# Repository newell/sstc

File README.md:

# sstc
This project is my design of a half-bridge Solid State Tesla Coil (SSTC).

An SSTC is a type of [Tesla coil](https://en.wikipedia.org/wiki/Tesla_coil) that uses modern semiconductor devices such as MOSFETs or IGBTs to generate high-frequency alternating current (AC) and high voltages. The term "half-bridge" refers to the specific configuration of the power electronics used in the coil.

## Tools Used for SSTC Design

- **[KiCad](https://github.com/KiCad)**: For schematic capture and PCB layout.
- **[build123d](https://github.com/gumyr/build123d)**: For CAD design.
- **[Prusa MK3S+](https://www.prusa3d.com/)**: 3D printer for printing the enclosure.

## How Half-Bridge SSTCs Work

1. **Power Supply**: The primary coil is powered by a DC power supply. This DC voltage is then switched on and off at a high frequency by the half-bridge circuit.

2. **Half-Bridge Configuration**:
   - **Half-Bridge Circuit**: The half-bridge circuit consists of two semiconductor switches (typically MOSFETs or IGBTs) and two capacitors. One switch is connected to the positive rail of the power supply, and the other switch is connected to the negative rail. The junction between the two switches connects to one end of the primary coil.
   - **Switching**: The switches are controlled in such a way that they turn on and off alternately. When one switch is on, it allows current to flow through the primary coil in one direction, and when the other switch is on, it allows current to flow in the opposite direction. This creates an alternating current (AC) in the primary coil.

3. **Resonant Circuit**: The primary coil and the primary capacitor form a resonant circuit. The switching frequency of the half-bridge circuit is typically set to match the resonant frequency of this LC circuit, which maximizes the energy transfer to the secondary coil.

4. **Secondary Coil**: The secondary coil, which is coupled to the primary coil via magnetic induction, has many more turns than the primary coil. This step-up transformer action increases the voltage to very high levels.

5. **Top Load**: The top load (usually a toroid) of the secondary coil helps to shape the electric field and allows the coil to produce long electrical discharges (sparks).

### Why It’s Called "Half-Bridge"

The term "half-bridge" comes from the structure of the circuit:
- **Full-Bridge vs. Half-Bridge**: In a full-bridge circuit, there are four switches arranged in an H-bridge configuration. This allows for full control over the direction of the current through the load (primary coil). In contrast, a half-bridge circuit uses only two switches and two capacitors. It controls the current direction by alternately switching the two switches, but only half of the H-bridge is implemented.
- **Simplified Design**: The half-bridge design is simpler and more cost-effective compared to a full-bridge design, making it a popular choice for SSTCs.

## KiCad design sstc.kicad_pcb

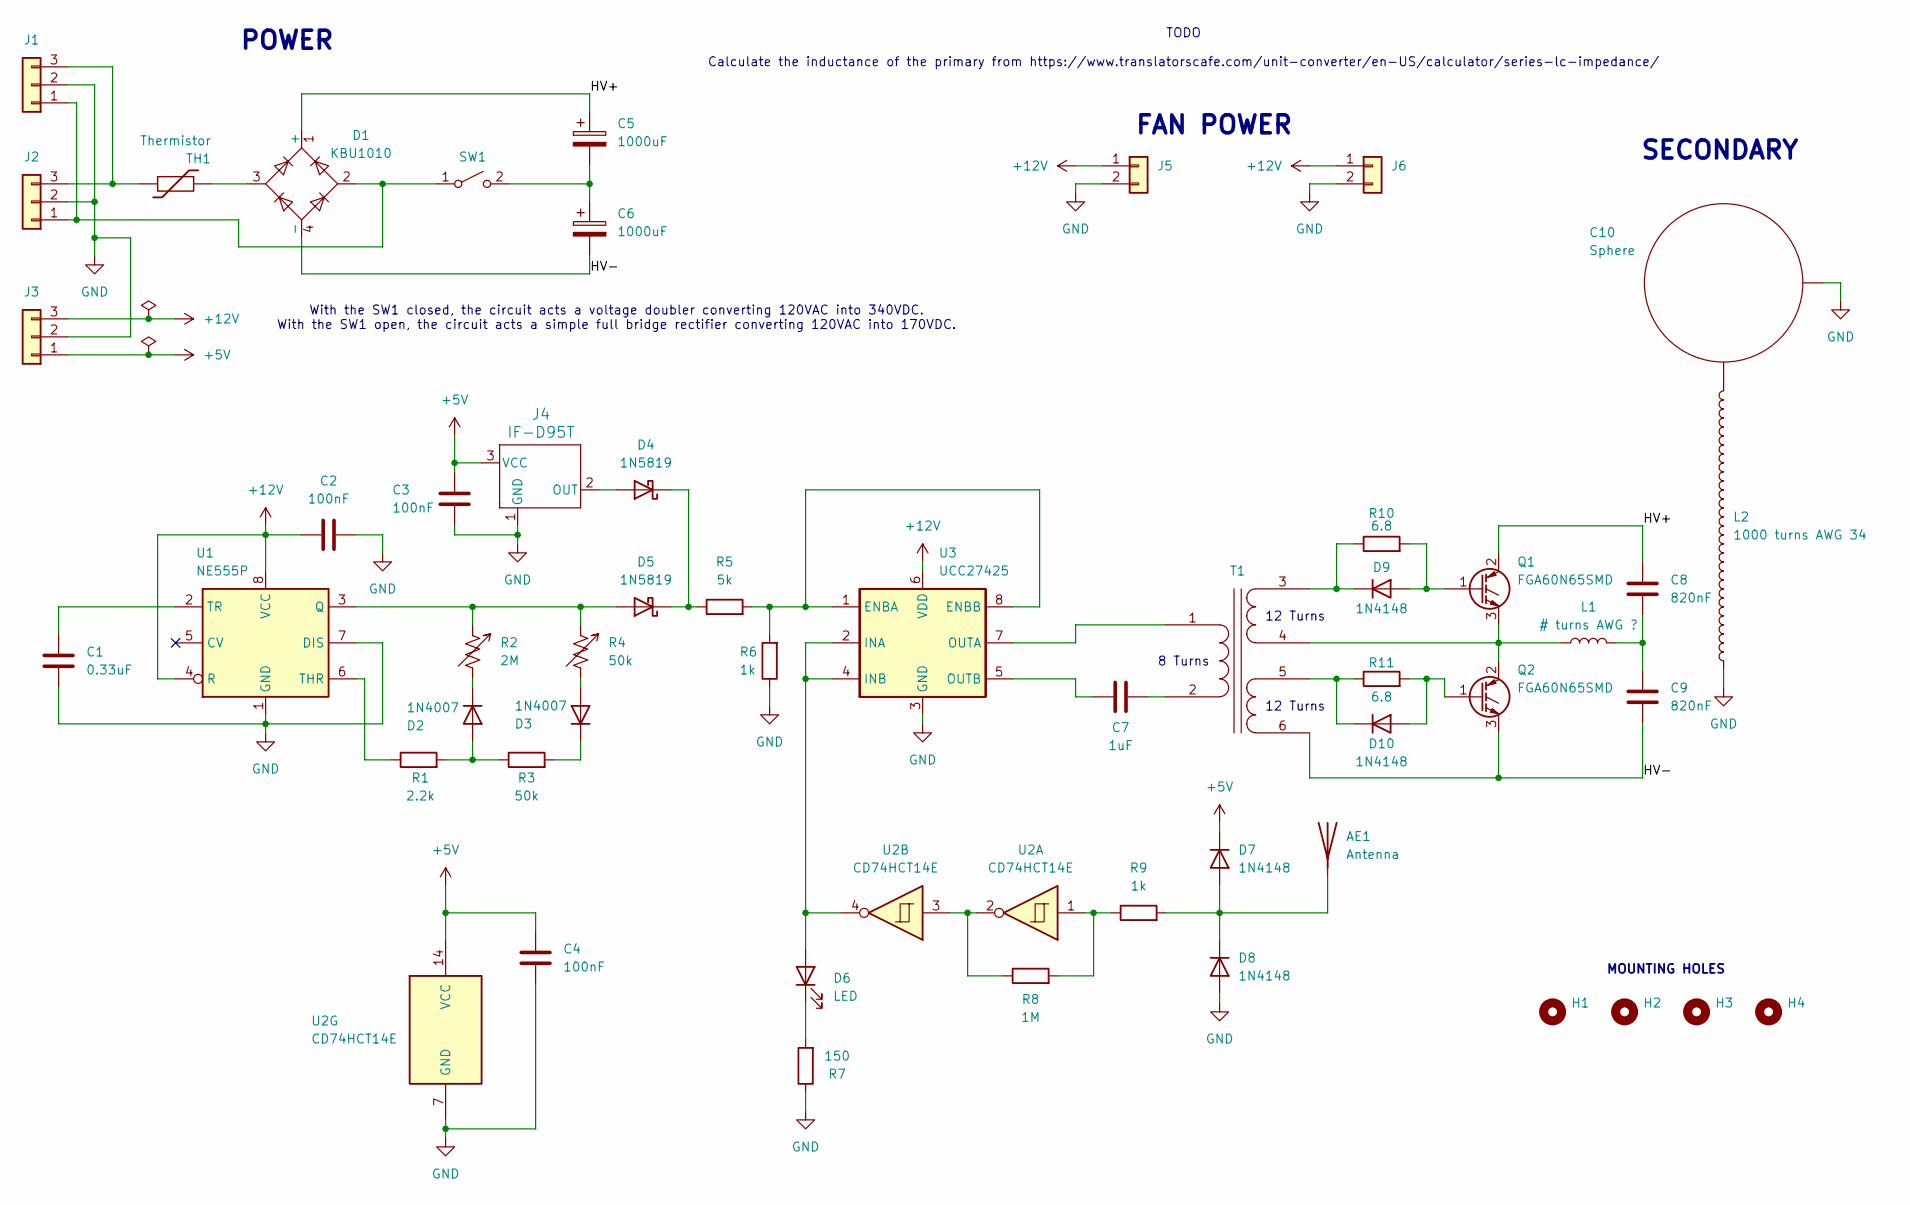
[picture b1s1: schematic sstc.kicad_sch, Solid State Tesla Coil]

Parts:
AE1: Antenna; SolderWire-1sqmm_1x01_D1.4mm_OD3.9mm
C1: 0.33uF; C_Rect_L7.0mm_W3.5mm_P5.00mm
C2, C3, C4: 100nF; C_Rect_L7.0mm_W3.5mm_P5.00mm
C5, C6: 1000uF; CP_Radial_D30.0mm_P10.00mm_SnapIn
C7: 1uF; C_Rect_L7.0mm_W3.5mm_P5.00mm
C8, C9: 820nF; C_Rect_L18.0mm_W11.0mm_P15.00mm_FKS3_FKP3
C10: Sphere
D1: KBU1010; Diode_Bridge_Vishay_KBU
D2, D3: 1N4007; D_DO-41_SOD81_P10.16mm_Horizontal
D4, D5: 1N5819; D_DO-41_SOD81_P10.16mm_Horizontal; Manufacturer_Part_Number 1N5819-TP
D6: LED; D_DO-35_SOD27_P7.62mm_Horizontal
D7, D8, D9, D10: 1N4148; D_DO-35_SOD27_P7.62mm_Horizontal
H1, H2, H3, H4: MountingHole; MountingHole_3.2mm_M3_ISO7380_Pad_TopBottom
J1, J2, J3: Conn_01x03; SolderWire-1sqmm_1x03_P7.8mm_D1.4mm_OD3.9mm
J4: IF-D95T; IF-D95T_IFB
J5, J6: Conn_01x02; JST_XH_B2B-XH-A_1x02_P2.50mm_Vertical
L1: # turns AWG ?; SolderWire-2sqmm_1x02_P7.8mm_D2mm_OD3.9mm
L2: 1000 turns AWG 34
Q1, Q2: FGA60N65SMD; TO-3P-3_Vertical
R1: 2.2k; R_Axial_DIN0614_L14.3mm_D5.7mm_P15.24mm_Horizontal
R2: 2M; R_Axial_DIN0614_L14.3mm_D5.7mm_P15.24mm_Horizontal
R3, R4: 50k; R_Axial_DIN0614_L14.3mm_D5.7mm_P15.24mm_Horizontal
R5: 5k; R_Axial_DIN0614_L14.3mm_D5.7mm_P15.24mm_Horizontal
R6, R9: 1k; R_Axial_DIN0614_L14.3mm_D5.7mm_P15.24mm_Horizontal
R7: 150; R_Axial_DIN0614_L14.3mm_D5.7mm_P15.24mm_Horizontal
R8: 1M; R_Axial_DIN0614_L14.3mm_D5.7mm_P15.24mm_Horizontal
R10, R11: 6.8; R_Axial_DIN0614_L14.3mm_D5.7mm_P15.24mm_Horizontal
SW1: SW_SPST; SolderWire-0.75sqmm_1x02_P4.8mm_D1.25mm_OD2.3mm
T1: Transformer_1P_2S; Transformer_NF_ETAL_P3324
TH1: Thermistor; R_Axial_DIN0411_L9.9mm_D3.6mm_P7.62mm_Vertical
U1: NE555P; DIP-8_W7.62mm
U2: CD74HCT14E; DIP-14_W7.62mm
U3: UCC27425; DIP-8_W7.62mm

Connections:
+5V: C3.1, C4.1, D7.1 (K), J3.1, J4.3 (VCC), U2.14 (VCC)
+12V: C2.1, J3.3, J5.1, J6.1, U1.4 (R), U1.8 (VCC), U3.6 (VDD)
/HV+: C5.1, C8.1, D1.1 (+), Q1.2 (C)
/HV-: C6.2, C9.2, D1.4 (-), Q2.3 (E), T1.6 (SD)
GND: C1.2, C2.2, C3.2, C4.2, C10.1, D8.2 (A), J1.2, J2.2, J3.2, J4.1 (GND), J5.2, J6.2, L2.1, R6.1, R7.1, U1.1 (GND), U1.7 (DIS), U2.7 (GND), U3.3 (GND)
unnamed: AE1.1 (A), D7.2 (A), D8.1 (K), R9.2
unnamed: C8.2, C9.1, L1.2
unnamed: C10.2, L2.2
unnamed: D1.3, TH1.1
unnamed: D2.2 (A), R1.2, R3.1
unnamed: D2.1 (K), R2.2
unnamed: D3.2 (A), R4.2
unnamed: D3.1 (K), R3.2
unnamed: D4.2 (A), J4.2 (OUT)
unnamed: D4.1 (K), D5.1 (K), R5.1
unnamed: D5.2 (A), R2.1, R4.1, U1.3 (Q)
unnamed: D6.2 (A), U2.4, U3.2 (INA), U3.4 (INB)
unnamed: D6.1 (K), R7.2
unnamed: D9.2 (A), Q1.1 (G), R10.2
unnamed: D9.1 (K), R10.1, T1.3 (SA)
unnamed: D10.2 (A), Q2.1 (G), R11.2
unnamed: D10.1 (K), R11.1, T1.5 (SC)
unnamed: D1.2, J1.1, J2.1, SW1.1 (A)
unnamed: J1.3, J2.3, TH1.2
unnamed: L1.1, Q1.3 (E), Q2.2 (C), T1.4 (SB)
unnamed: R8.1, U2.2, U2.3
unnamed: R8.2, R9.1, U2.1
unnamed: C5.2, C6.1, SW1.2 (B)
unnamed: T1.1 (AA), U3.7 (OUTA)
unnamed: C7.2, T1.2 (AB)
unnamed: R1.1, U1.6 (THR)
unnamed: C1.1, U1.2 (TR)
unnamed: R5.2, R6.2, U3.1 (ENBA), U3.8 (ENBB)
unnamed: C7.1, U3.5 (OUTB)

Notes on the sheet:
With the SW1 closed, the circuit acts a voltage doubler converting 120VAC into 340VDC. With the SW1 open, the circuit acts a simple full bridge rectifier converting 120VAC into 170VDC.
TODO Calculate the inductance of the primary from https://www.translatorscafe.com/unit-converter/en-US/calculator/series-lc-impedance/
12 Turns
POWER
MOUNTING HOLES
FAN POWER
SECONDARY
8 Turns

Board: 2 copper layers, 50 parts (0 on the bottom side), 33 nets, no tracks yet.

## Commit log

2024-07-30 Add Kicad project
2024-07-30 CAD initial commit
2024-07-30 Update schematic and round corners on PCB edge cuts
